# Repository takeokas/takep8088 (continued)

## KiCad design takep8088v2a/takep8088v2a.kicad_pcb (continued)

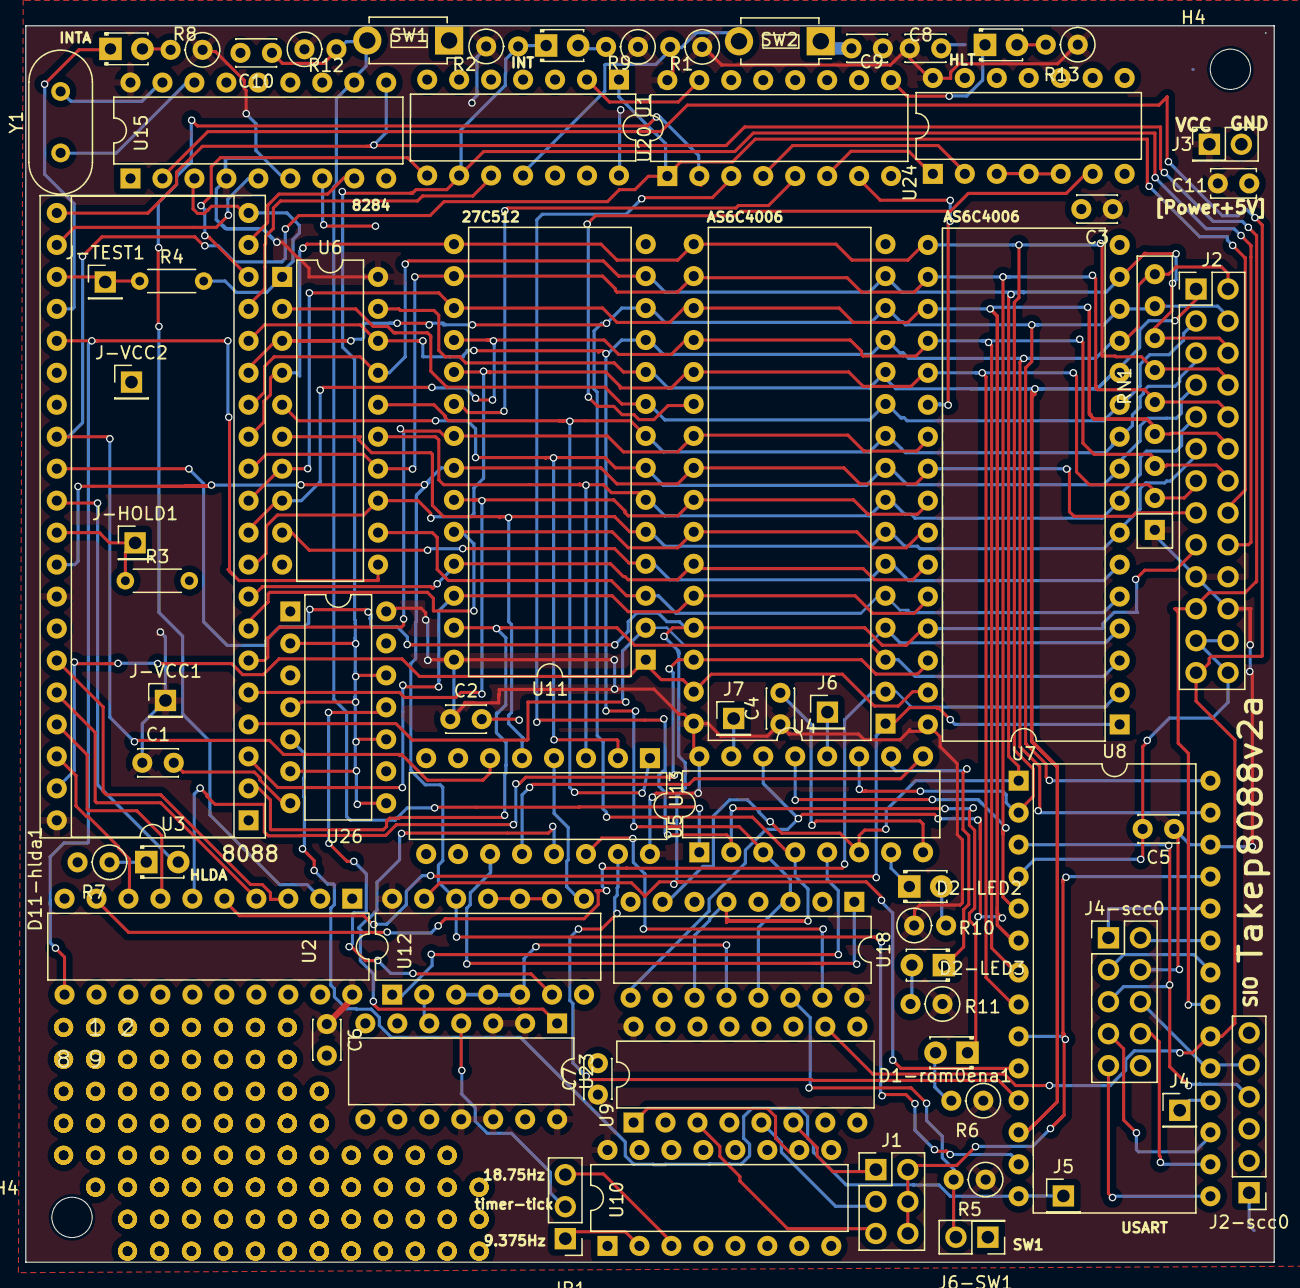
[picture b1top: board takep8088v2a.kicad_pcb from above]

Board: 2 copper layers, 99.2 x 98.2 mm, 167 parts (0 on the bottom side), 105 nets.

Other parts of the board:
1, 2, 3, 4, 5, 6, 7, 8, 9, 10, 11, 12, 13, 14, 15, 16, 17, 18, 19, 20, 21, 22, 23, 24, 25, 26, 27, 28, 29, 30, 31, 32, 33, 34, 35, 36, 37, 38, 39, 41, 42, 43, 44, 45, 46, 47, 48, 49, 50, 51, 52, 53, 54, 55, 56, 57, 58, 59, 60, 61, 62, 63, 64, 65, 66, 67, 68, 69, 70, 71, 72, 73, 74, 75, 76, 77, 78, 79, 81, 82, 83, 84, 85, 86, 87, 88, 89, 90, 91, 92, 93, 94, 95, 96, 97, 98: (no value)
H4, H4#2: MountingHole; MountingHole_3.2mm_M3

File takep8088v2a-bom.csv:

#,Reference,Qty,Value,Comment,購入URL,Footprint,DNP
1,"C1, C2, C3, C4, C5, C6, C7, C8, C9",9,C,,,Capacitor_THT:C_Disc_D3.0mm_W2.0mm_P2.50mm,
2,C10,1,10uF,,,Capacitor_THT:C_Disc_D3.0mm_W2.0mm_P2.50mm,
3,C11,1,CP,,,Capacitor_THT:C_Disc_D3.4mm_W2.1mm_P2.50mm,
4,"D1-rom0ena1, D2-int1, D2-LED2, D2-LED3, D11-hlda1, D13-inta1, LED-halt1",7,LED,,,LED_THT:LED_D1.8mm_W3.3mm_H2.4mm,
5,J1,1,"HEADER_3x2,PH-2x3SG",USART ボーレート・ジェネレータ入力周波数 選択,https://akizukidenshi.com/catalog/g/g116883/,Connector_PinHeader_2.54mm:PinHeader_2x03_P2.54mm_Vertical,
6,J2,1,HEADER_13x2,IO拡張コネクタ。適当に好きなもの,,Connector_PinHeader_2.54mm:PinHeader_2x13_P2.54mm_Vertical,
7,J2-scc0,1,"HEADER_6,PH-1X6RG(2)",SIOコネクタ。FTDI USBシリアル・ケーブルが適合,https://akizukidenshi.com/catalog/g/g105336/,Connector_PinHeader_2.54mm:PinHeader_1x06_P2.54mm_Vertical,
8,J3,1,HEADER_2,+5V電源入力。適当に好きなもの,,Connector_PinHeader_2.54mm:PinHeader_2x01_P2.54mm_Vertical,
9,"J4, J5, J6, J7, J-HOLD1, J-TEST1, J-VCC1, J-VCC2",8,-,test pointなので、何も実装しない,,,
10,J4-scc0,1,-,test pointなので、何も実装しない,,Connector_PinHeader_2.54mm:PinHeader_2x05_P2.54mm_Vertical,
11,JP1,1,"HEADER_1x3,PH-1X3SG",free running timerのレート選択,https://akizukidenshi.com/catalog/g/g103949/,Connector_PinHeader_2.54mm:PinHeader_1x03_P2.54mm_Vertical,
12,"R1, R2, R5, R12",4,"R,10K",,,Resistor_THT:R_Axial_DIN0207_L6.3mm_D2.5mm_P2.54mm_Vertical,
13,"R3, R4",2,"R,4.7K",,,Resistor_THT:R_Axial_DIN0204_L3.6mm_D1.6mm_P5.08mm_Horizontal,
14,"R6, R7, R8, R9, R10, R11, R13",7,"R,330",,,Resistor_THT:R_Axial_DIN0207_L6.3mm_D2.5mm_P2.54mm_Vertical,
15,RN1,1,R_Network08,,,Resistor_THT:R_Array_SIP9,
16,SW1,1,TVBP06-B043CU-B,Reset,https://akizukidenshi.com/catalog/g/g108214/,Button_Switch_THT:SW_PUSH_1P1T_6x3.5mm_H5.0_APEM_MJTP1250,
17,SW2,1,TVBP06-B043CU-B,NMI_SW,https://akizukidenshi.com/catalog/g/g108214/,Button_Switch_THT:SW_PUSH_1P1T_6x3.5mm_H5.0_APEM_MJTP1250,
18,U1,1,74LS14,,,Package_DIP:DIP-14_W7.62mm,
19,"U2, U6",2,74LS373,,,Package_DIP:DIP-20_W7.62mm,
20,U3,1,8088,,https://wakamatsu.biz/products/detail/455907,Package_DIP:DIP-40_W15.24mm_Socket,
21,"U4, U7",2,AS6C4008,Aliexpressで買っても、およそ大丈夫,,Package_DIP:DIP-32_W15.24mm,
22,U5,1,74LS174,74HC174でも可,,Package_DIP:DIP-16_W7.62mm,
23,U8,1,8251A,,,Package_DIP:DIP-28_W15.24mm,
24,"U9, U10",2,4040,,,Package_DIP:DIP-16_W7.62mm,
25,U11,1,27C512,,,Package_DIP:DIP-28_W15.24mm,
26,"U12, U14",2,74HC00,,,,
27,U13,1,74LS138,,,Package_DIP:DIP-16_W7.62mm,
28,U15,1,8284,,https://wakamatsu.biz/products/detail/456508,Package_DIP:DIP-18_W7.62mm,
29,U18,1,74LS367,,,Package_DIP:DIP-16_W7.62mm,
30,U20,1,74LS139,一部入力ピンがopenなので、必ずLS。または、「役立たない配線」をするなら、LSでも可,,Package_DIP:DIP-16_W7.62mm,
31,U23,1,74HC74,,,Package_DIP:DIP-14_W7.62mm,
32,U26,1,74LS05,HCでも可。LSであっても、空き入力ピンは、必ずLoにすること。,,Package_DIP:DIP-14_W7.62mm,
33,Y1,1,"Crystal,14.7456MHz",,,Crystal:Crystal_HC49-4H_Vertical,
34,U24,1,74LS00,一部入力ピンがopenなので、必ずLS,,,
35, J6-SW1,1,,適当なスイッチを無理やり取付ける,,,

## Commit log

2026-03-20 Expand README with specs and circuit details
    Added detailed specifications and circuit information for the 8088 Single Board Computer.
2026-03-20 Schematic
2026-03-20 Board Photo upload
2026-03-20 Add images and update specifications in README
2026-03-20 Update README with crystal and CPU frequency info
    Add details about the crystal frequency and CPU operation.
2026-03-20 Fix formatting in README.md for clarity
2026-03-20 Update README with board details and image
    Added board section with jumper information and image.
2026-03-20 Update README with PullDown clarification for 7405
    Clarified the need for PullDown on open terminals of 7405.
2026-03-20 Fix formatting of jumper descriptions in README
2026-03-20 Update README with SIO 8251 and timer information
    Added details about SIO 8251 and free-running timer settings.
2026-03-20 Update README with wire design notes and HOLD info
    Added notes about wire connections and HOLD functionality.
2026-03-20 Update jumper J1 description in README
    Corrected the description of jumper J1 to specify clock frequency selection.
2026-03-20 Update image width and fix text formatting in README
2026-03-20 Rename IMG_8818.jpg to front.jpg
2026-03-20 Rename IMG_8819.jpg to back.jpg
2026-03-20 Rename takep88v2.zip to gerber.zip
2026-03-22 Update Makefile
2026-03-22 Create README.md for Xmodem program loader
    Add README for program loader via Xmodem with usage instructions.
2026-03-22 Fix LED indicator description in README
2026-03-22 Update README with FTDI USB serial converter details
    Added information about FTDI USB serial converter and its compatibility.
2026-03-22 Fix formatting in README for USART section
2026-03-31 Revise Xmodem program description in README
    Updated Xmodem program details and usage instructions in README.
